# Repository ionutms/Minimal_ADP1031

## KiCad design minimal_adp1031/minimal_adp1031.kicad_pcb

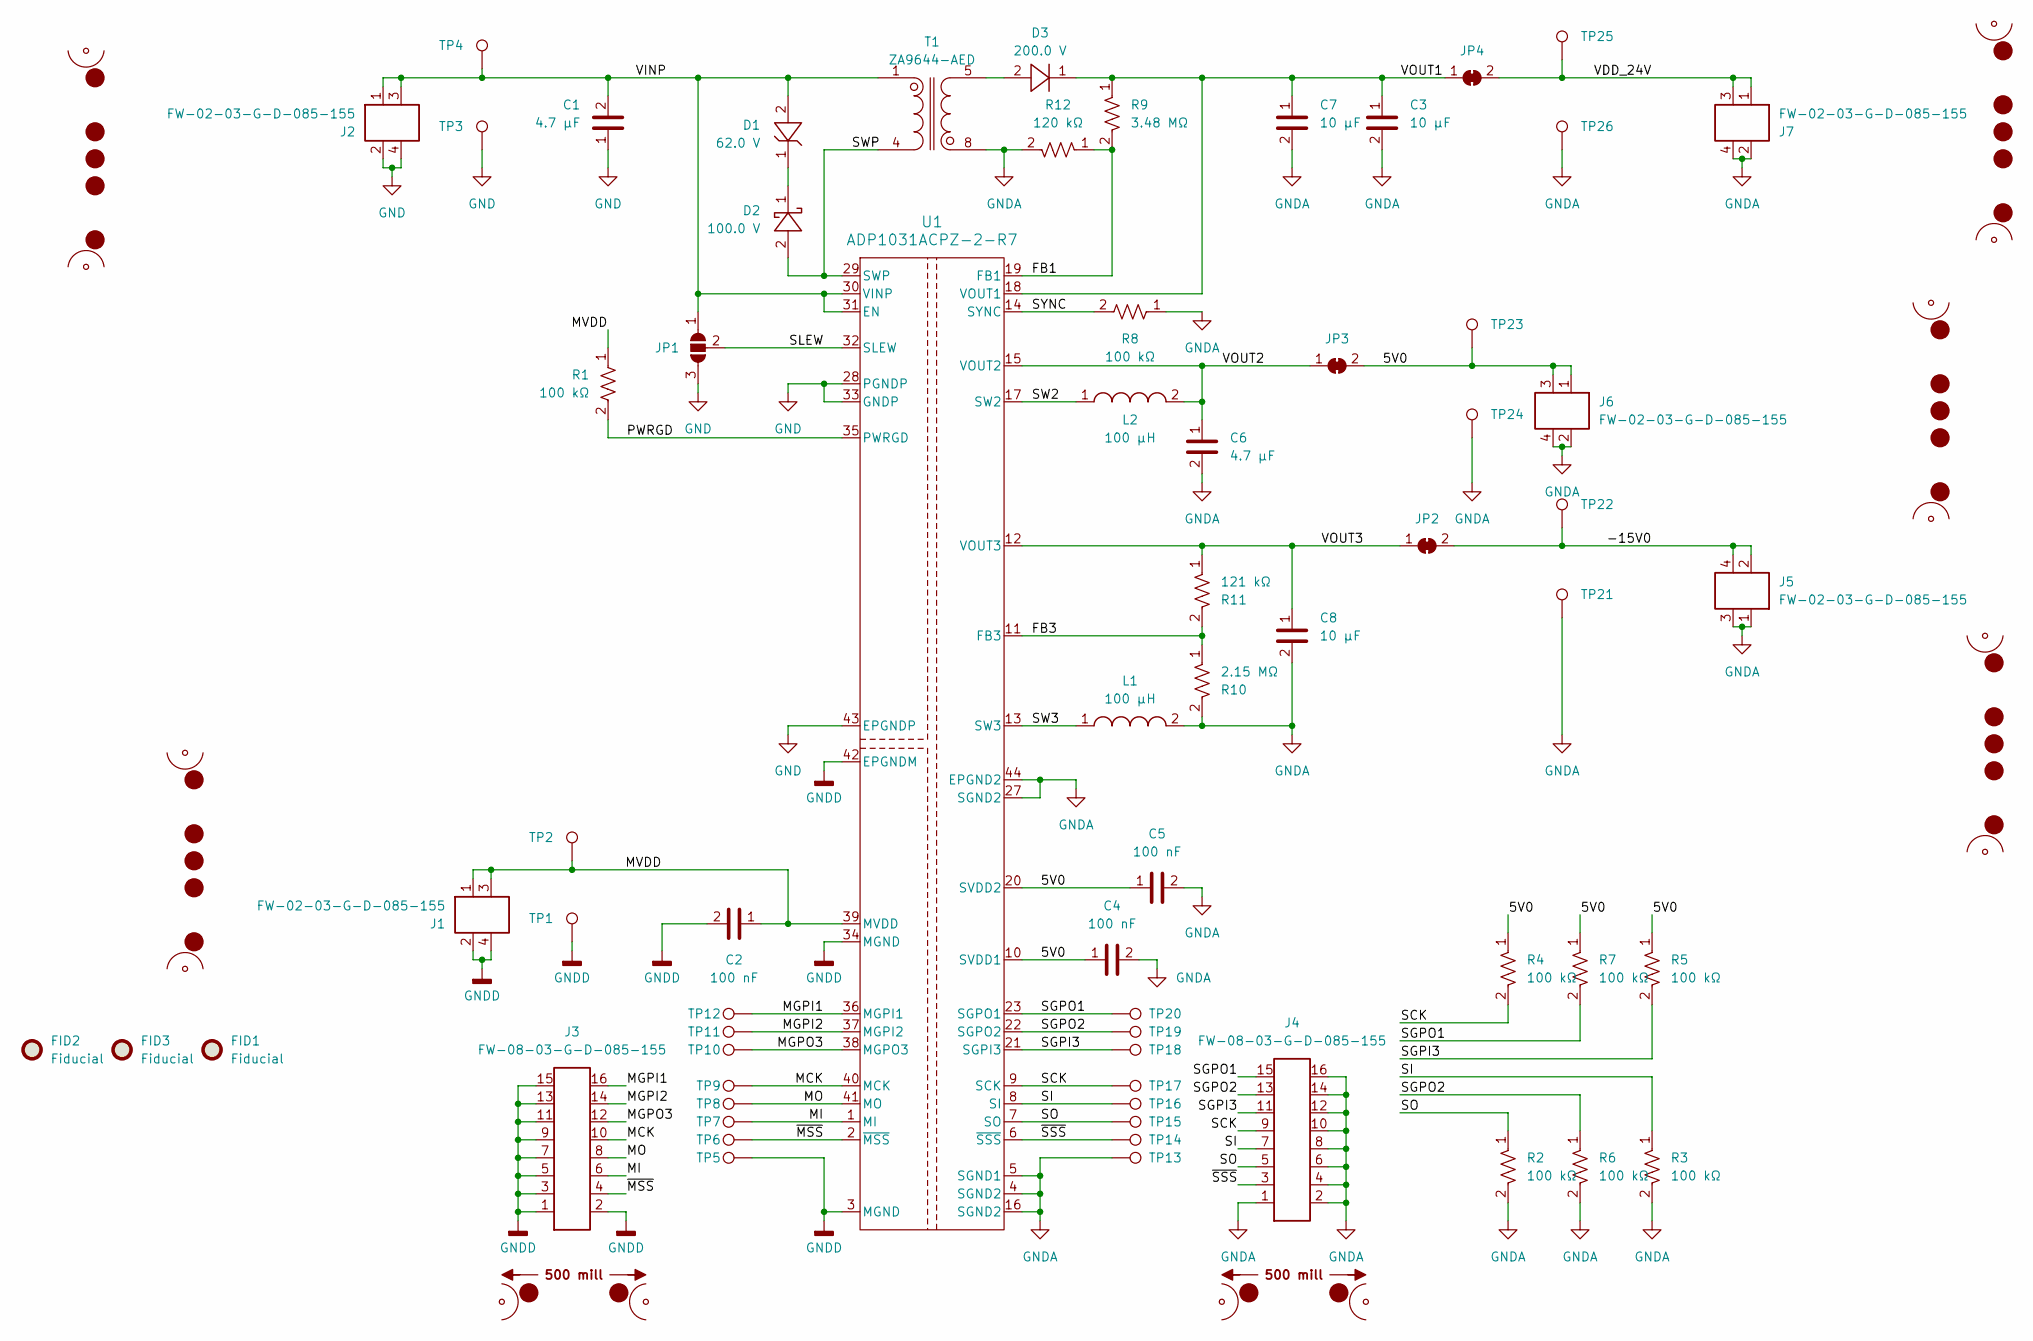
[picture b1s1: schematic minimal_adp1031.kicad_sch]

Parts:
C1: 4.7 µF; C_1210_200_3225Metric; Tolerance 10%; Voltage Rating 100V; MPN GCM32DC72A475KE02K
C2, C4, C5: 100 nF; C_0402_1005Metric; Voltage Rating DC 50 VDC; Tolerance 10%; MPN GCM155R71H104KE02D
C3, C7, C8: 10 µF; C_1206_3216Metric; Voltage Rating DC 50 VDC; Tolerance 10%; MPN CL31B106KBHNNN#
C6: 4.7 µF; C_0603_1608Metric; Voltage Rating DC 10 VDC; Tolerance 10%; MPN C1608X7S1A475K080AC
D1: 62.0 V; SOD_123; MPN MMSZ5265BT1G
D2: 100.0 V; PowerDI_123; MPN DFLS1200-7
D3: 200.0 V; SOD_123F; MPN US1DWF
FID1, FID2, FID3: Fiducial; Fiducial_0.5mm_Mask1mm
J1, J2, J5, J6, J7: FW-02-03-G-D-085-155; Current Rating (A) 5.2; Voltage Rating (V) 300; MPN FW-02-03-G-D-085-155
J3, J4: FW-08-03-G-D-085-155; Current Rating (A) 5.2; Voltage Rating (V) 300; MPN FW-08-03-G-D-085-155
JP1: SolderJumper_3_Open; SolderJumper-3_P1.3mm_Open_RoundedPad1.0x1.5mm_NumberLabels
JP2, JP3, JP4: SolderJumper_2_Bridged; SolderJumper-2_P1.3mm_Bridged_RoundedPad1.0x1.5mm
L1, L2: 100 µH; XFL3012; Tolerance ±20%; MPN XFL3012-104ME
MB1, MB2, MB5, MB6, MB7: mouse-bite-midle-50mil-200mil; mouse-bite-50mil-305mil
MB3, MB4: mouse-bite-50mil-450mil; mouse-bite-50mil-500mil
R1, R2, R3, R4, R5, R6, R7, R8: 100 kΩ; R_0402_1005Metric; Voltage Rating 50V; Tolerance 5%; MPN ERJ-2GEJ104X
R9: 3.48 MΩ; R_0402_1005Metric; Tolerance 1%; Voltage Rating 50V; MPN RC0402FR-073M48L
R10: 2.15 MΩ; R_0402_1005Metric; Tolerance 1%; Voltage Rating 50V; MPN RC0402FR-072M15L
R11: 121 kΩ; R_0402_1005Metric; Tolerance 1%; Voltage Rating 50V; MPN ERJ-2RKF1213X
R12: 120 kΩ; R_0402_1005Metric; Tolerance 1%; Voltage Rating 50V; MPN ERJ-2RKF1203X
T1: ZA9644-AED; ZA9644; Tolerance ±10%; MPN ZA9644-AED
TP1, TP2, TP3, TP4, TP5, TP6, TP7, TP8, TP9, TP10, TP11, TP12, TP13, TP14, TP15, TP16, TP17, TP18, TP19, TP20, TP21, TP22, TP23, TP24, TP25, TP26: TestPoint; TestPoint_THTPad_Castelated
U1: ADP1031ACPZ-2-R7; CP-41-1_ADI; MPN ADP1031ACPZ-2-R7

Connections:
/5V0: C4.1, C5.1, J6.1, J6.3, JP3.2, R4.1, R5.1, R7.1, TP23.1, U1.10 (SVDD1), U1.20 (SVDD2), U1.26 (DNC)
/-15V0: J5.2, J5.4, JP2.2, TP22.1
/FB1: R9.2, R12.1, U1.19 (FB1)
/FB3: R10.1, R11.2, U1.11 (FB3)
/MCK: J3.10, TP9.1, U1.40 (MCK)
/MGPI1: J3.16, TP12.1, U1.36 (MGPI1)
/MGPI2: J3.14, TP11.1, U1.37 (MGPI2)
/MGPO3: J3.12, TP10.1, U1.38 (MGPO3)
/MI: J3.6, TP7.1, U1.1 (MI)
/MO: J3.8, TP8.1, U1.41 (MO)
/MVDD: C2.1, J1.1, J1.3, R1.1, TP2.1, U1.39 (MVDD)
/PWRGD: R1.2, U1.35 (PWRGD)
/SCK: J4.9, R4.2, TP17.1, U1.9 (SCK)
/SGPI3: J4.11, R5.2, TP18.1, U1.21 (SGPI3)
/SGPO1: J4.15, R7.2, TP20.1, U1.23 (SGPO1)
/SGPO2: J4.13, R6.1, TP19.1, U1.22 (SGPO2)
/SI: J4.7, R3.1, TP16.1, U1.8 (SI)
/SLEW: JP1.2 (C), U1.32 (SLEW)
/SO: J4.5, R2.1, TP15.1, U1.7 (SO)
/SW2: L2.1, U1.17 (SW2)
/SW3: L1.1, U1.13 (SW3)
/SWP: D2.2, T1.4, U1.29 (SWP)
/SYNC: R8.2, U1.14 (SYNC)
/VDD_24V: J7.1, J7.3, JP4.2, TP25.1
/VINP: C1.2, D1.2, J2.1, J2.3, JP1.1 (A), T1.1, TP4.1, U1.30 (VINP), U1.31 (EN)
/VOUT1: C3.1, C7.1, D3.1, JP4.1, R9.1, U1.18 (VOUT1)
/VOUT2: C6.1, JP3.1, L2.2, U1.15 (VOUT2)
/VOUT3: C8.1, JP2.1, R11.1, U1.12 (VOUT3)
/~MSS: J3.4, TP6.1, U1.2 (~MSS)
/~SSS: J4.3, TP14.1, U1.6 (~SSS)
GND: C1.1, J2.2, J2.4, JP1.3 (B), TP3.1, U1.28 (PGNDP), U1.33 (GNDP), U1.43 (EPGNDP)
GNDA: C3.2, C4.2, C5.2, C6.2, C7.2, C8.2, J4.1, J4.2, J4.4, J4.6, J4.8, J4.10, J4.12, J4.14, J4.16, J5.1, J5.3, J6.2, J6.4, J7.2, J7.4, L1.2, R2.2, R3.2, R6.2, R8.1, R10.2, R12.2, T1.8, TP13.1, TP21.1, TP24.1, TP26.1, U1.4 (SGND2), U1.5 (SGND1), U1.16 (SGND2), U1.27 (SGND2), U1.44 (EPGND2)
GNDD: C2.2, J1.2, J1.4, J3.1, J3.2, J3.3, J3.5, J3.7, J3.9, J3.11, J3.13, J3.15, TP1.1, TP5.1, U1.3 (MGND), U1.34 (MGND), U1.42 (EPGNDM)
unnamed: D1.1, D2.1
unnamed: D3.2, T1.5

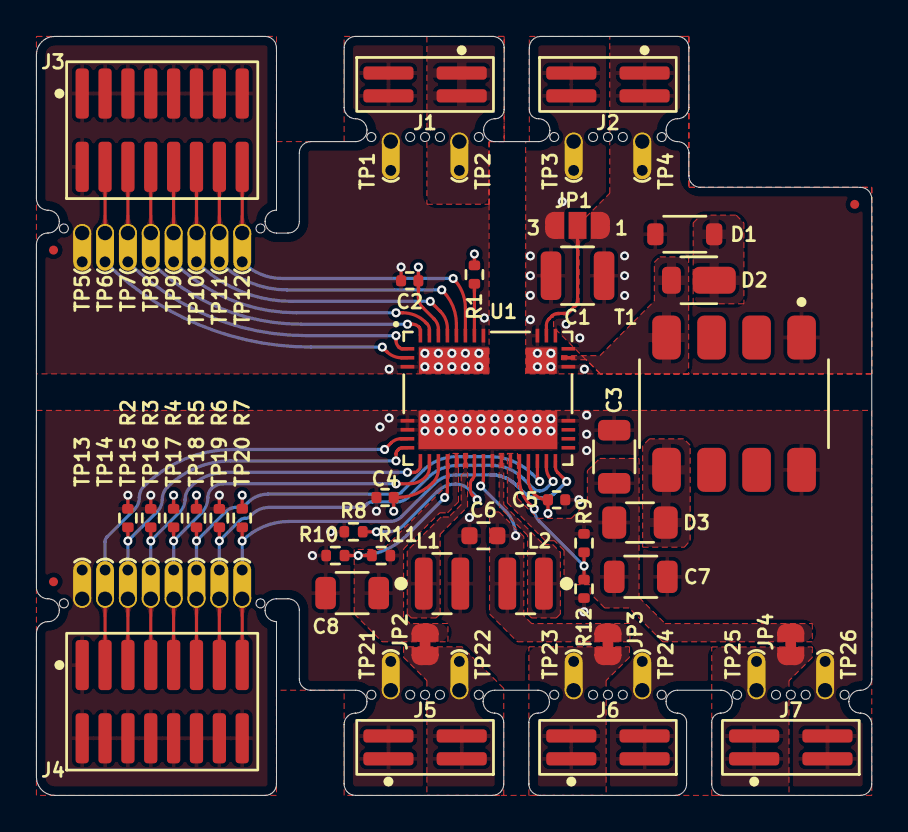
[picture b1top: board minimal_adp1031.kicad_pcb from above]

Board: 4 copper layers, 46.4 x 42.2 mm, 74 parts (0 on the bottom side), 35 nets.

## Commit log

2025-08-20 Add initial KiCad project files and GitHub workflows
2025-08-20 Update KiCad documentation for minimal_adp1031 (schematics and PCB renders)
2025-08-20 backup
2025-08-21 Add .github/.env to .gitignore to exclude environment files from version control
2025-08-22 Update KiCAD workflow configurations
2025-08-28 Update KiCAD workflow files for ADP1031 project
2025-10-05 chore: update workflows from central repository
2025-10-05 chore: update workflows and kicad config from central repository
2025-10-26 Update kicad-config workflow settings
